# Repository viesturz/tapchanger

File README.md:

# Tapchanger

A nozzle Z probe + toolchanger for Voron 2.

## Features
* Off the shelf voron parts, except for bearings.
* Uses [Dragon Burner](https://github.com/chirpy2605/voron/tree/main/V0/Dragon_Burner) toolhead - can fit 6 hotends in 350 frame. [Stealthburner](https://github.com/VoronDesign/Voron-Stealthburner) and MiniStealthburner 
are an option but limited support. (Experimental version of the [Rapid Burner](https://github.com/chirpy2605/voron/tree/main/V0/Rapid_Burner) is in the works by @Marshalldog) (Experimental version for the [Xol-Toolhead](https://github.com/Armchair-Engineering/Xol-Toolhead) is in the works)
* Uses [OptoTap](https://www.google.com/search?q=optotap) probe sensor for nozzle Z probing.
* Same [rigidity](https://youtu.be/mGRXtK9F408) and probe accuracy as Tap.
* Same external printer dimensions, except for top hat.
* No servos, no wires on the shuttle, recommended to use with a Canbus toolhead board for less wires, but anything goes.

# Build guide

I would recommend to get a single hotend working first:

* Check the [BOM](/Tapchanger/BOM.md).
* [Print](./Print%20Guide.md) the parts.
* [Assemble](/Tapchanger/Assembly.md) it.

Multiple tools setup:
* Install [Umbilical](/Umbilical/Umbilical.md).
* Install [Docks](/Dock/Dock.md)
* Add a [TopHat](/TopHat/TopHat.md)
* Configure [Klipper](/Klipper/README.md)
* Calibrate the offsets. I'm using [this](https://github.com/viesturz/NozzleAlign)

# Community

Improvement ideas - bugs, pull requests welcome. Find me on [Voron Toolchangers Discord](https://discord.gg/xmDWrYGwVJ), or file bugs here.

See Tapchanger [youtube channel](https://www.youtube.com/playlist?list=PLqU7kX5nUJDRDw5z0NLwJ22OkV6fbjnSW).

# Credits

- Basic models from [Voron Stealthburner](https://github.com/VoronDesign/Voron-Stealthburner) and [Voron 0](https://github.com/VoronDesign/Voron-0).
- Mini SB Orbiter cowling form [mozartlovescats](https://www.printables.com/model/366337-voron-02-orbiter-20-trianglelab-chc-mini-stealthbu).
- Mini SB LGX lite cowling form [MC](https://www.printables.com/model/395933-voron-02-mini-stealthburner-remix-for-lgx-light-ex/files).
- Dragon Burner from [chirpy2605](https://github.com/chirpy2605/voron/tree/main/V0/Dragon_Burner).
- HGX gears extruder derived from [nhchiu's ProtoXtruder](https://github.com/nhchiu/VoronMods/tree/main/Extruders/ProtoXtruder)

# How does this work?

It's essentially an oversized linear rail, that supports only ~4 mm of travel. The steel rail is replaced by bearings riding on rods.

In addition, it's a kinematic mount, meaning that it's self aligning and there is no play even if the parts are not aligned precisely.

# Revision history:

## V4.3
Dragon burner printability, ease of assembly tweaks:
* Two piece mount plate with less supports needed
* Better access to the heatset inserts
* Slightly larger sensor screw holes to better work with polycarbonate
* Will need to reprint the cowling as well, slight changes there

## V4.2
Small tweaks across the board:
* Dragon toolhead mount plate 1mm thicker - no interferance with fans and 8mm tensioning screws do not stick out
* Fix shuttle mounting plate misalignment, thanks [vikwin](https://github.com/vikwin) for spotting
* Alternative version for the PFTE tube holder at the side
* Dock for RapidBurner
* Extras
  * Better ventilated EBB36 shield 
  * Improved strain relief for HGX + DragonBurner
  * More Stepper gear distance adjustability for HGX + DragonBurner.

Dragon burner toolhead exploded view: 

## V4.1
HGX gears + Dragon + EBB36 [optimized toolhead](/Tapchanger/STL/Toolheads/DragonBurner/HGX%20Gears/):

* 17 mm shorter filament path
* 17 grams lighter than stock, only 2 screws
* Integrated harness strain relief
* Integrated EBB36 mount & shield
* Bambu & Revo adapters only for now
* There will be some supports to remove.

## V4.0
[Liftbar dock](/Dock/Liftbar/Liftbar.md)

Other minor DragonBurner changes:
* More clearance around the hookon slot.
* More room around the cooling fans, to avoid cracking the cowling when tightening the bottom screws.
* More sturdy dock.

## V3.2
Introduces support for the Experimental Rapid Burner Toolhead by @Marshalldog.

## V3.1
End of year update, lots of small printability, clearance, etc updates. 
This is a stable version.

* Migrated to Dragon V8 hotend.
* More clearance around the OptoTap sensor.
* Tuning of the tension screw angles to minimize the docking resistance.
* More clearance for big block hotends.
* Hook-on dock is now the recommended for DragonBurner.

## V3.0

Further improvements to DragonBurner toolhead and dock.
The screw head locking mechanism is back.
Configuration updated, with better dock pathing.

The Dragon Burner toolhead is now the default. Let me know if you would like to see backports.

## V2.9

Improved DragonBurner toolhead and dock, adding bottom mounting screws for better stability.
Needs the modified cowling now.

## V2.8

# Added Tophat and Ubmilical, it's now a Printer!

## V2.5

* Added top mounted dock. see updated Dock folder.
* Slight tweaks square rods mounting plate for easier fit.

## V2.3 - Nozzle pads upgraded to springsteel ones, no more melting.

## V2.2 - Square rods version added.

Option to use square rods for better contact surface for the bearings.  Shares the shuttle and bearings with rods.

There are now total of 3 versions:
 - Plates - bigger bearings, more work to make the plates and assemble. The rolling surface is not great. Very rigid.
 - Rods - smaller bearings, easiest to assemble, but more flex.
 - Square rods - middle ground between plates and rods, the rigidity testing was done with this.

## V2.1 - Rods fixes.

Various fixes to refine the rods version. Ready for general testing.

## V2 - Rods version added.

A new experimental version using 3mm rods. See -rods files. Shuttle and mount plates changed, the rest is same.

- Easier to assemble
- Tension adjustment screws easily available
- Runs smoother
- Using smaller 3x8x3 bearings - saves 5 grams and even more rigid.
- Even load distribution between the bearings by adjusting the angles to 26 and 64 degrees.

## V1.1 - Verified and cleaned up.

- Minor model tweaks for better fit and printability.

## V1 - This should work

- Redesigned and optimized - not compatible with V0
- Significanly more rigid
- Supports both Mini and full size Stealthburner

## V0 - Initial drop
 
 - It can print and looks reasonably rigid
 - ~10 Tool chnages so far
 - Initial dock, that looks okay for the job

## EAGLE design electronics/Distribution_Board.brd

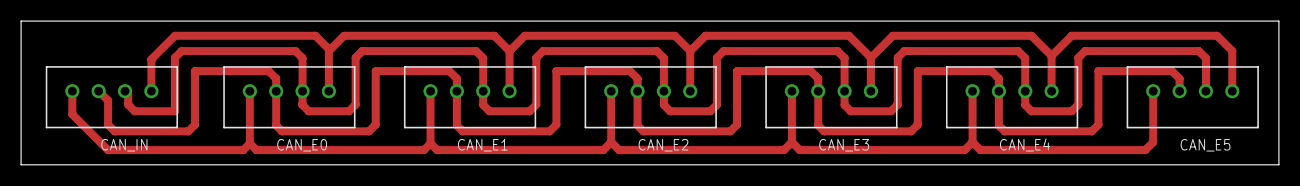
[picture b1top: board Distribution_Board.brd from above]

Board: 2 copper layers, 119.4 x 13.6 mm, 7 parts (0 on the bottom side), 4 nets.

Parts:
CAN_E0, CAN_E1, CAN_E2, CAN_E3, CAN_E4, CAN_E5: 3A/250V; B4B-XH-A
CAN_IN: 3A/250V; B4B-XH-A

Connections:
unnamed: CAN_E0.1, CAN_E1.1, CAN_E2.1, CAN_E3.1, CAN_E4.1, CAN_E5.1, CAN_IN.1
unnamed: CAN_E0.2, CAN_E1.2, CAN_E2.2, CAN_E3.2, CAN_E4.2, CAN_E5.2, CAN_IN.2
unnamed: CAN_E0.4, CAN_E1.4, CAN_E2.4, CAN_E3.4, CAN_E4.4, CAN_E5.4, CAN_IN.4
unnamed: CAN_E0.3, CAN_E1.3, CAN_E2.3, CAN_E3.3, CAN_E4.3, CAN_E5.3, CAN_IN.3

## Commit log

2023-03-26 Initial Cad version
2023-03-26 Initial STLs
2023-03-26 Shuttle assembly instructions
2023-03-26 Update STLs
2023-03-26 Inital dock version
2023-03-26 Dock tweaks.
2023-03-27 Dock change. Add wipe pad.
2023-03-27 Update pics
2023-03-27 Front pins pic
2023-03-28 New tip pad design
2023-03-30 Dock tweaks. Initial cable strain relief.
2023-03-31 Minor tweaks
2023-04-03 Add youtube link
2023-04-03 Strain releaf update
2023-04-06 Update strain relief, some folders.
2023-04-06 Distribution box first iteration.
2023-04-06 Bom in separate file.
2023-04-07 Tweaks to distribution box and adding a simple clip.
2023-04-07 Let's call it a 0.1
2023-04-08 Actual mounting solution. Updated dock to match.
2023-04-09 Prototype Boob version.
2023-04-10 Boob dock prototype
2023-04-10 Boop frame mount
2023-04-21 V0.2 First toolchanges confirmed.
2023-04-23 Update tool probe code. Quad gantry level works again.
2023-04-23 New preview
2023-04-23 Update config
2023-04-23 Fix z offset to work with homing.
2023-04-23 Homing now accounts for current tool Z offset.
2023-04-25 Dock v6
2023-04-26 Config fix
2023-04-28 Some dock tweaks
2023-04-28 More instructions.
2023-05-05 Update macros
2023-05-05 Update config readme
2023-05-08 Remove unnecesaary stuff from dock
2023-05-25 0.2.5
2023-05-25 Wiring info
2023-05-31 Add distribution board PCB
2023-05-31 Fix typo in canbus
2023-05-31 Add M568 macro and make sure there is an active tool
2023-06-01 Update config.
2023-06-02 Add 3.4mm thickness to the shuttle
2023-06-03 Add 8mm BHCS Shuttle option
2023-06-03 Update BOM for 8mm BHCS
2023-06-03 V2 first try
2023-06-04 Split dock to allow swapping upper part
2023-06-04 Split distribution box to make wiring easier
2023-06-04 Strain relief cads
2023-06-04 Add 5.6mm CableFlex part
2023-06-04 More consistent naming
2023-06-09 Update clips
2023-06-09 Mov rev2 to separate repo
2023-06-10 Rotate stls to correct print orientation
2023-06-11 Klipper update. Fixing some tools calibrate bugs.
2023-06-11 Don't clear out Z g-code offset before homing
2023-06-16 Make the tool config ~sane; TCLite support in config. Basic Z offset description.
2023-06-18 Add tube organizer
2023-06-18 Fix orientation
2023-06-25 Fixes to bowden tube organizer
2023-06-29 Restore only Z after toolchange.
2023-09-18 Lite is now main.
2023-09-18 Assembly instructions.
2023-09-18 Documentation fixes.
2023-09-18 Updated cads.
2023-09-18 Doc fixes.
2023-09-18 Update example printer config to support rods.
2023-09-18 Prototype CNC shuttle version
2023-09-19 Add square rods option.
2023-09-20 Add rods version.
2023-09-23 Tune the docking sequence a bit.
2023-09-23 Slightly righten the square rods slot, reduce screw angle from 0.5 to 0.2 deg
2023-09-23 Sync tools_calibrate.
2023-09-27 Add obj files.
2023-09-27 Update calibrate offsets script to output savable config changes.
2023-09-27 Update example config. Some cleanups after setting up all 6 tools. And wait for tool to come to temp before picking it up from dock.
2023-09-29 Tweaks to example config. Remove config for legacy toolchanger.
2023-10-01 New nozzle pads.
2023-10-02 Update dock instructions.
2023-10-02 V2.3
2023-10-02 Dragon burner test plate
2023-10-03 DragonBurner dev
2023-10-07 Dragon burner dev
2023-10-08 Dragon burner adapter v1
2023-10-12 Top anchored mounts WIP
2023-10-13 Enhancements to add Shuttle Keeper and Rear X Endstop Mount
2023-10-25 Tweak the aluminium shuttle.
2023-10-29 Dragon mount final tweaks.
2023-10-29 Small tweaks to all square rods - looser fit and more accurate adjustment screw angle.
2023-11-04 Move things around.
2023-11-04 Add Initial tophat and Umbilical
2023-11-05 Tophat WIP
2023-11-05 Umbilical WIP
2023-11-05 Documentation update.
2023-11-06 Umbilical - WIP.
2023-11-09 Umbilical refinements
2023-11-09 Small top dock improvements.
2023-11-12 2.8 - umbilical is done.
2023-11-12 Fix link
2023-11-19 Add round rods mount for DragonBurner.
2023-11-27 Move all the klipper extensions to a single repo.
2023-11-27 Fix folders.
2023-11-30 Add ebb36 cover.
2023-12-01 Move the hook on dock to experimental.
2023-12-08 Redo the hook on dock. Make the Dragon cowling universal.
2023-12-09 Further tweaks to hook on dock
2023-12-09 Updated config example. With support for hook on docking.
2023-12-09 More tweaks to cowling for hookon dock.
2023-12-10 Update documentation.
2023-12-10 Add hookon dock for crossbar
2023-12-11 Update the cad file.
2023-12-15 Add more clearance for shuttle middle legs to exit.
2023-12-17 Update example config.
2023-12-17 Macros updates
    * preheat all hotends in use
    * fix wait for hotend temp before undocking the tool.
    * larger max radius for docking approach/depart.
2023-12-21 Minor cleanups all across.
    - [All] better tensioning screw angle
    - [Dragon] migrate to DragonBurnerV8
    - [Dragon] move the ventilation gap next to the hotend to minimize heat transfer to the mount.
    - [All] fixed missing gap between OptoTap and the shuttle.
    - [All] slightly move OptoTap scew holes back
2023-12-21 Remove duplicate CAD
2023-12-23 Dragon burner mount plate: Trim off some material.
2023-12-27 [dev] Dual magnets version
2023-12-29 Add files via upload
    Improved rigidity (may have issues with led install)
2023-12-29 Add files via upload
    adds tool head latch mechanism from Dragon Burner
2023-12-29 Add files via upload
    clean up on the design
2024-01-06 Add cad for umbilical.
2024-01-06 Deprecate magnets dock for DB
2024-01-19 add tapchanger-rods xol-toolhead dock, maglock faceplate and base
    add tapchanger-rods xol-toolhead dock, maglock faceplate and base (experimental, only for tapchanger-(lite)-rods)
2024-01-19 add tool-path to xol readme
    add xol docking tool-path to xol readme
2024-01-20 Tapchanger-kiss
2024-01-24 Add some functionality
    - Add x to possible path values for future dock types
    - Change so default is always 0 for all paths, to simplify paths
    - Add DROPOFF/PICKUP START/END macros that can be used with rename to add user code to these calls for LEDS, Runout Sensors, Nozzle cleaning or other tasks
2024-02-04 Liftbar prototype
2024-02-05 Brace + Idlers update
    More clearance and endstop slot.
2024-02-06 Add 20T variant.
2024-02-06 Fix brace slide width to 6.2mm.
2024-02-10 add input shaper type to example toolchanger.cfg, T0.cfg, T1.cfg
    changes to example toolchanger.cfg, T0.cfg, T1.cfg
    add add support for input shaper type to tools. defaults to params in toolchanger.cfg if shaper params are not set in tool.
2024-02-10 Liftbar next iteration.
2024-02-10 Remove distribution board, this is not suitable for the amps it will be pulling.
2024-02-11 Renames
2024-02-17 add shaper damping ratio as optional tool param
    add shaper damping ratio as optional tool param
2024-02-18 Top hat tweaks
2024-02-18 Dev liftbar
2024-02-19 More sturdy optotap mount for SB
2024-02-20 Added a Top Hat Pillar variant for 18 inch pannel commonly found in hardware store. Also documented insert and screw count.
2024-02-20 fixed some typo for the new Top Hat pillar
2024-02-21 Change = to : for proper yaml
2024-02-23 Adding Misschanger compatibility
    This commit adds the path and gcode commands for Misschanger.
    NEED TESTING BEFORE MERGING. I tried not to cause any changes to the other toolchangers. Nevertheless, as the movement-related gcodes have been reshuffled, it is best to be cautious with this commit.
2024-02-23 Bug Fix
    Prevent the bug where the firmware would crashes if T0 is done before homing.
2024-02-23 Bug fixes
    Prevent the bug where the firmware would crashes if T0 is done before homing.
2024-02-23 Bug fixes
    Prevent the bug where the firmware would crashes if T5 is done before homing.
2024-02-23 Bug Fixes
2024-02-23 Bug fixes
    Prevent the bug where the firmware would crashes if toolchange is done before homing.
2024-02-23 Bug fixes
    Prevent the bug where the firmware would crashes if tool-change is done before homing.
2024-03-02 Liftbar V0.1
2024-03-09 DragonBurner dock redesign - way more alignment clearance.
2024-03-09 Liftbar 0.2 - it's working!
2024-03-11 Liftbar 0.2
2024-03-11 Revert "DragonBurner dock redesign - way more alignment clearance."
    This reverts commit b80ea15ed5b037be775f1505a19a4ce3a0c08461.
2024-03-15 Add second gearbox, bottom endstops
2024-03-15 Update dual magnets mount
2024-03-15 More robust pad clip
2024-03-17 Liftbar - add secondary motor.
2024-03-17 Dragonburner - Updated hook interface.
    Provides room for about 1mm offset in XZ.
2024-03-30 Add toolhead strain relief for DB
2024-03-30 Dragon Burner dock tweaks.
2024-03-30 Larger wire hole
2024-04-02 More clearance at the dock legs.
2024-04-05 Add Trident XY idlers.
2024-04-05 Tweak the iders.
2024-04-06 Liftbar - getting out of dev.
2024-04-06 More documentation.
2024-04-06 Finalize DragionBurner dock design.
2024-04-06 V4.0
2024-04-08 Update ebb36 cover
2024-04-15 4.1 - HGX hears + DragonBurner
2024-04-21 Dragon burner - Landing new cowling & dock.
2024-04-21 Update config example.
2024-04-21 Add gearbox lid.
2024-04-22 Add dragon mount
2024-05-04 Update BOM.md
    Fix an error in rods dimension
2024-05-07 Add cad for HGX
2024-05-08 Fix orientation.
2024-05-08 Add ProtoXtruder to credits.
2024-05-08 Shuttle tweaks
    Move the old stuff away, improve printability a bit. Update the Aluminium model to 2 magnets.
2024-05-08 Spelling
2024-05-12 HGX gears update.
2024-05-12 Update Back+5mm.stl
    Fix orientation
2024-05-12 HGX gears strain relief tweaks.
2024-05-16 Fix shuttle base misalignment.
    Fixes #44
2024-05-17 Added Belt keeper optimized shuttles.
2024-05-18 Move extras to extras.
2024-05-18 Add 1 mm to Dragon Burner back plate - more clearance for the fans and adjustment screws.
2024-05-19 Add 1mm extra spacing around the motor to accomodate bigger motors.
2024-05-20 RapidBurner docks
2024-05-20 Side holder v2
2024-05-20 Revert "RapidBurner docks"
    This reverts commit d88aca647cb9b013e654e3f454001fa21dd06c89.
2024-05-20 Add RapidBurner docks
2024-05-24 Fix some print orientations.
2024-05-25 Add shuttle assembly jig.
2024-05-27 Add belt helper
2024-05-28 Belt Helper tweaks.
2024-06-09 Misc tweaks.
2024-06-10 Add liftbar assembly cad.
2024-06-16 Dragon burner - Better printability with polycarbonate.
2024-06-28 Small Dragon burner updates.
2024-07-17 HGX 2 extruder
2024-07-20 Add dragonfly BMO mount.
2024-11-05 Dual loop gantry
    Adding a dual loop gantry with independent motors and endstops.
2024-11-09 Liftbar consmetic cleanup.
2024-11-25 6mm tube harness and dual loop liftbar.
2025-01-18 Trident servo lifter
2025-01-18 Some trident tweaks
2025-01-22 add Trident liftbar hat
2025-01-22 Update README.md
    Add showcases in README
2025-02-01 Remove the steel wire from 6mm umbilical.
2025-02-01 Fix examples link
2025-02-21 5mm version.
2025-04-12 Rename umbilical folders.
2025-04-18 Add CAD files for tophat
2025-04-19 Add step file for tophat
